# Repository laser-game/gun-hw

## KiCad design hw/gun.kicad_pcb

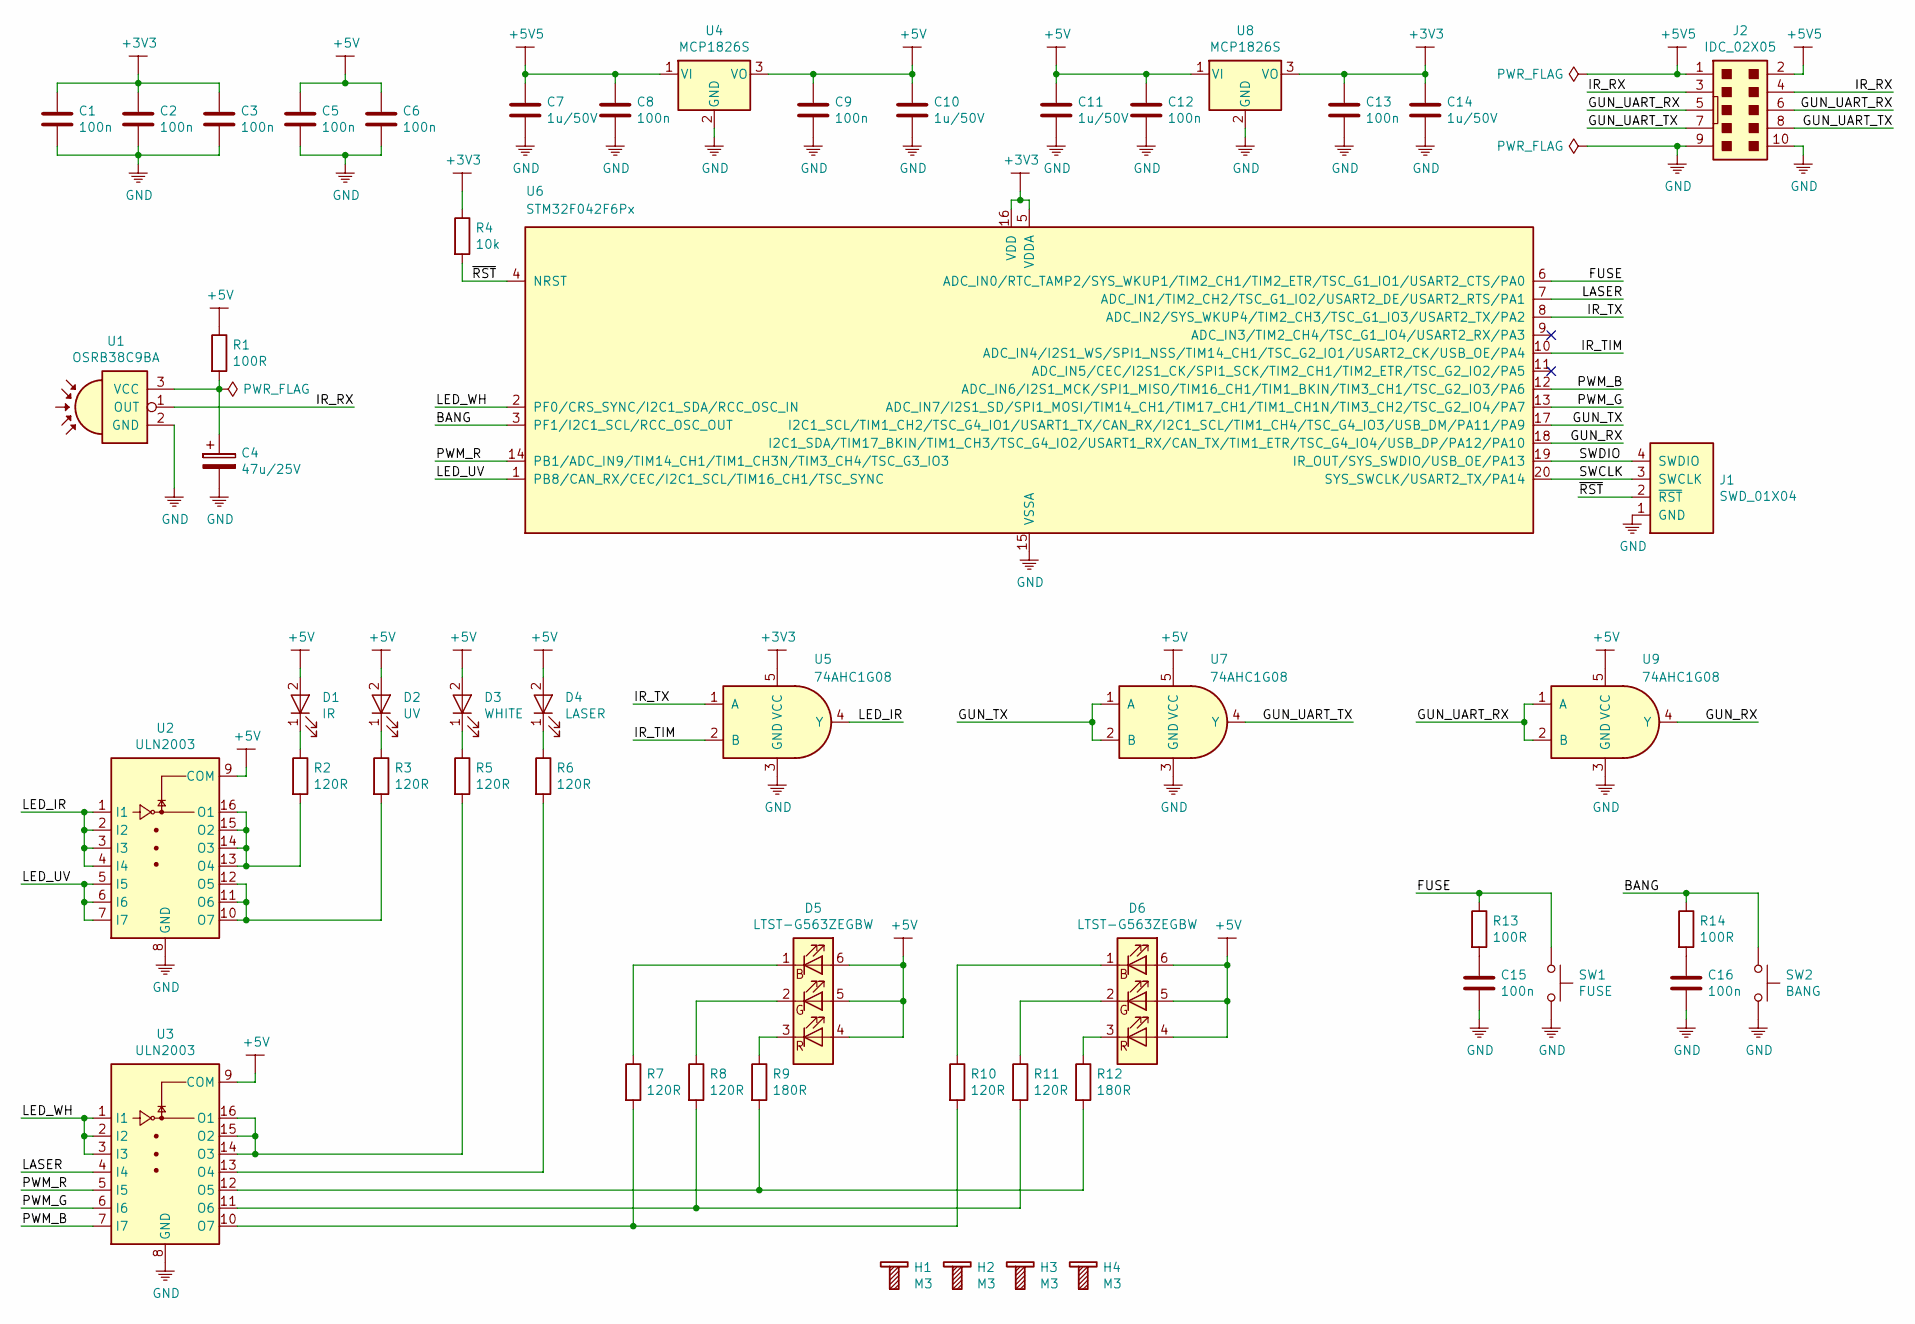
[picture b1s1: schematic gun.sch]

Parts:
C1, C2, C3, C5, C6, C8, C9, C12, C13, C15, C16: 100n; C_0805_2012Metric
C4: 47u/25V; CP_EIA-7343-31_Kemet-D
C7, C10, C11, C14: 1u/50V; C_0805_2012Metric
D1: IR; PinHeader_1x02_P2.54mm_Vertical
D2: UV; PinHeader_1x02_P2.54mm_Vertical
D3: WHITE; PinHeader_1x02_P2.54mm_Vertical
D4: LASER; PinHeader_1x02_P2.54mm_Vertical
D5, D6: LTST-G563ZEGBW; LED_RGB_5050-6
H1, H2, H3, H4: M3; Bolt_M3
J1: SWD_01X04; PinHeader_1x04_P2.54mm_Vertical
J2: IDC_02X05; IDC-Header_2x05_P2.54mm_Vertical
R1, R13, R14: 100R; R_0805_2012Metric
R2, R3, R5, R6: 120R; R_1210_3225Metric
R4: 10k; R_0805_2012Metric
R7, R8, R10, R11: 120R; R_0805_2012Metric
R9, R12: 180R; R_0805_2012Metric
SW1: FUSE; PinHeader_2x01_P2.54mm_Vertical
SW2: BANG; PinHeader_2x01_P2.54mm_Vertical
U1: OSRB38C9BA; OSRB8C9BA_Vertical
U2, U3: ULN2003; SOIC-16_3.9x9.9mm_P1.27mm
U4, U8: MCP1826S; SOT-223-3_TabPin2
U5, U7, U9: 74AHC1G08; SOT-23-5
U6: STM32F042F6Px; TSSOP-20_4.4x6.5mm_P0.65mm

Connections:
+3V3: C1.1, C2.1, C3.1, C13.1, C14.1, R4.1, U5.5 (VCC), U6.5 (VDDA), U6.16 (VDD), U8.3 (VO)
+5V: C5.1, C6.1, C9.1, C10.1, C11.1, C12.1, D1.2 (A), D2.2 (A), D3.2 (A), D4.2 (A), D5.4 (BA), D5.5 (GA), D5.6 (RA), D6.4 (BA), D6.5 (GA), D6.6 (RA), R1.1, U2.9 (COM), U3.9 (COM), U4.3 (VO), U7.5 (VCC), U8.1 (VI), U9.5 (VCC)
+5V5: C7.1, C8.1, J2.1, J2.2, U4.1 (VI)
/BANG: R14.1, SW2.1, U6.3 (PF1/I2C1_SCL/RCC_OSC_OUT)
/FUSE: R13.1, SW1.1, U6.6 (ADC_IN0/RTC_TAMP2/SYS_WKUP1/TIM2_CH1/TI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)
/GUN_RX: U6.18 (I2C1_SDA/TIM17_BKIN/TIM1_CH3/TSC_G4_IO2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), U9.4 (Y)
/GUN_TX: U6.17 (I2C1_SCL/TIM1_CH2/TSC_G4_IO1/USART1_TX/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), U7.1 (A), U7.2 (B)
/GUN_UART_RX: J2.5, J2.6, U9.1 (A), U9.2 (B)
/GUN_UART_TX: J2.7, J2.8, U7.4 (Y)
/IR_RX: J2.3, J2.4, U1.1 (OUT)
/IR_TIM: U5.2 (B), U6.10 (ADC_IN4/I2S1_WS/SPI1_NSS/TIM14_CH1/TSC_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)
/IR_TX: U5.1 (A), U6.8 (ADC_IN2/SYS_WKUP4/TIM2_CH3/TSC_G1_IO3/U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)
/LASER: U3.4 (I4), U6.7 (ADC_IN1/TIM2_CH2/TSC_G1_IO2/USART2_DE/U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)
/LED_IR: U2.1 (I1), U2.2 (I2), U2.3 (I3), U2.4 (I4), U5.4 (Y)
/LED_UV: U2.5 (I5), U2.6 (I6), U2.7 (I7), U6.1 (PB8/CAN_RX/CEC/I2C1_SCL/TIM16_CH1/TSC_S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)
/LED_WH: U3.1 (I1), U3.2 (I2), U3.3 (I3), U6.2 (PF0/CRS_SYNC/I2C1_SDA/RCC_OSC_IN)
/PWM_B: U3.7 (I7), U6.12 (ADC_IN6/I2S1_MCK/SPI1_MISO/TIM16_CH1/TI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)
/PWM_G: U3.6 (I6), U6.13 (ADC_IN7/I2S1_SD/SPI1_MOSI/TIM14_CH1/TIM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)
/PWM_R: U3.5 (I5), U6.14 (PB1/ADC_IN9/TIM14_CH1/TIM1_CH3N/TIM3_CH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)
/SWCLK: J1.3 (SWCLK), U6.20 (SYS_SWCLK/USART2_TX/PA14)
/SWDIO: J1.4 (SWDIO), U6.19 (IR_OUT/SYS_SWDIO/USB_OE/PA13)
/~RST: J1.2 (~RST), R4.2, U6.4 (NRST)
GND: C1.2, C2.2, C3.2, C4.2, C5.2, C6.2, C7.2, C8.2, C9.2, C10.2, C11.2, C12.2, C13.2, C14.2, C15.2, C16.2, J1.1 (GND), J2.9, J2.10, SW1.2, SW2.2, U1.2 (GND), U2.8 (GND), U3.8 (GND), U4.2 (GND), U5.3 (GND), U6.15 (VSSA), U7.3 (GND), U8.2 (GND), U9.3 (GND)
unnamed: C4.1, R1.2, U1.3 (VCC)
unnamed: C15.1, R13.2
unnamed: C16.1, R14.2
unnamed: D1.1 (K), R2.1
unnamed: D2.1 (K), R3.1
unnamed: D3.1 (K), R5.1
unnamed: D4.1 (K), R6.1
unnamed: D5.1 (RK), R7.1
unnamed: D5.2 (GK), R8.1
unnamed: D5.3 (BK), R9.1
unnamed: D6.1 (RK), R10.1
unnamed: D6.2 (GK), R11.1
unnamed: D6.3 (BK), R12.1
unnamed: R2.2, U2.13 (O4), U2.14 (O3), U2.15 (O2), U2.16 (O1)
unnamed: R3.2, U2.10 (O7), U2.11 (O6), U2.12 (O5)
unnamed: R5.2, U3.14 (O3), U3.15 (O2), U3.16 (O1)
unnamed: R6.2, U3.13 (O4)
unnamed: R7.2, R10.2, U3.10 (O7)
unnamed: R8.2, R11.2, U3.11 (O6)
unnamed: R9.2, R12.2, U3.12 (O5)

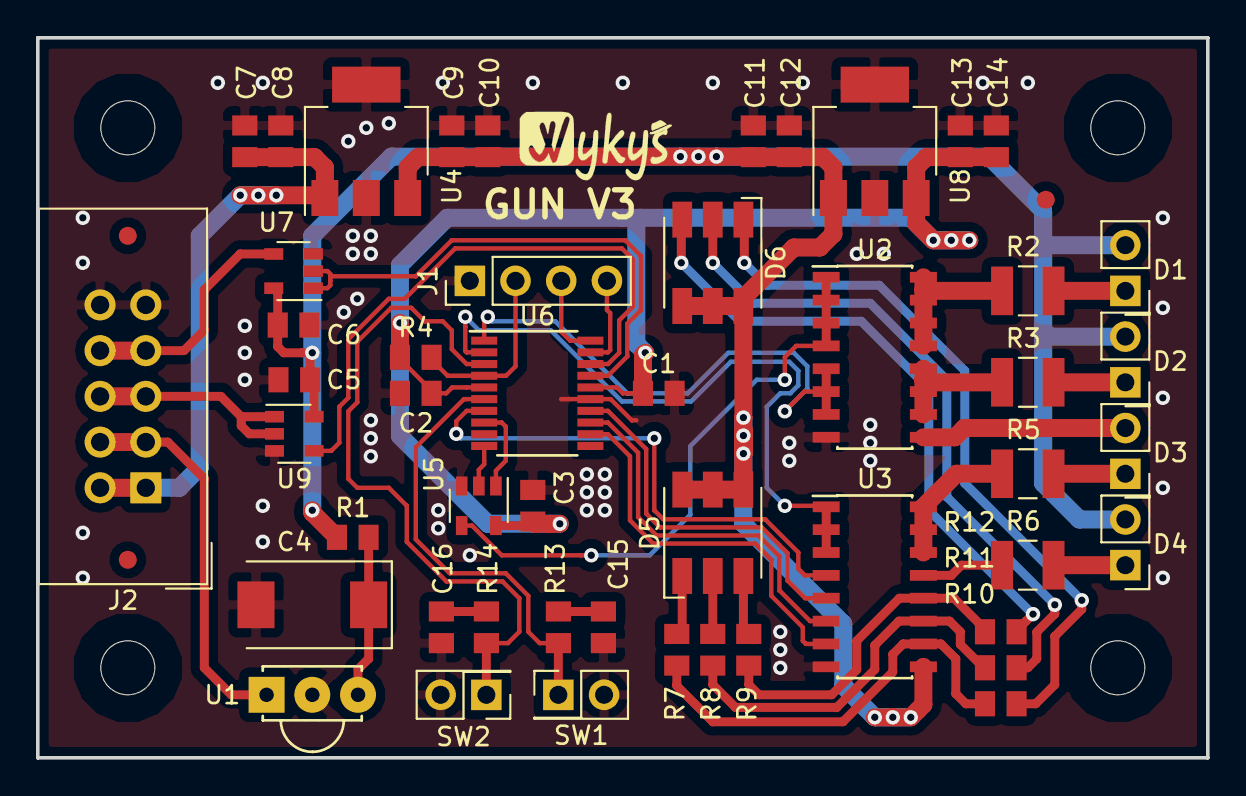
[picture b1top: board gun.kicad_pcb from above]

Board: 2 copper layers, 65.0 x 40.0 mm, 53 parts (0 on the bottom side), 43 nets.

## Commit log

2018-03-30 added license and updated readme
2018-04-01 added schematic
2018-04-18 updated .gitignore
2018-04-18 updated schematic
2018-04-18 updated pcb placement components
2018-04-18 updated pcb
2018-04-19 update pcb
2018-05-02 added boom file and schematic for fabracation
2018-05-08 added placement files
